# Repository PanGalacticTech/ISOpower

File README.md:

# ISOpowerProject
 Remote power control board for ISO experiment containers, used for remote labs projects

## Use

### Programming [See Issues]
 To Program AtMega328pb use the following settings:

### prog_power_select

- Jumper is used for power routing during programming
- Cut trace to main and solder USB to center to enable USB power during programming.
- Ensure to remove USB side and replace main for normal use

## Issues V1.0

1. Tx & Rx Pin swapped on CH340 - aTmeGA328P
 - To enable USB communication, reverse pins 2 & 3

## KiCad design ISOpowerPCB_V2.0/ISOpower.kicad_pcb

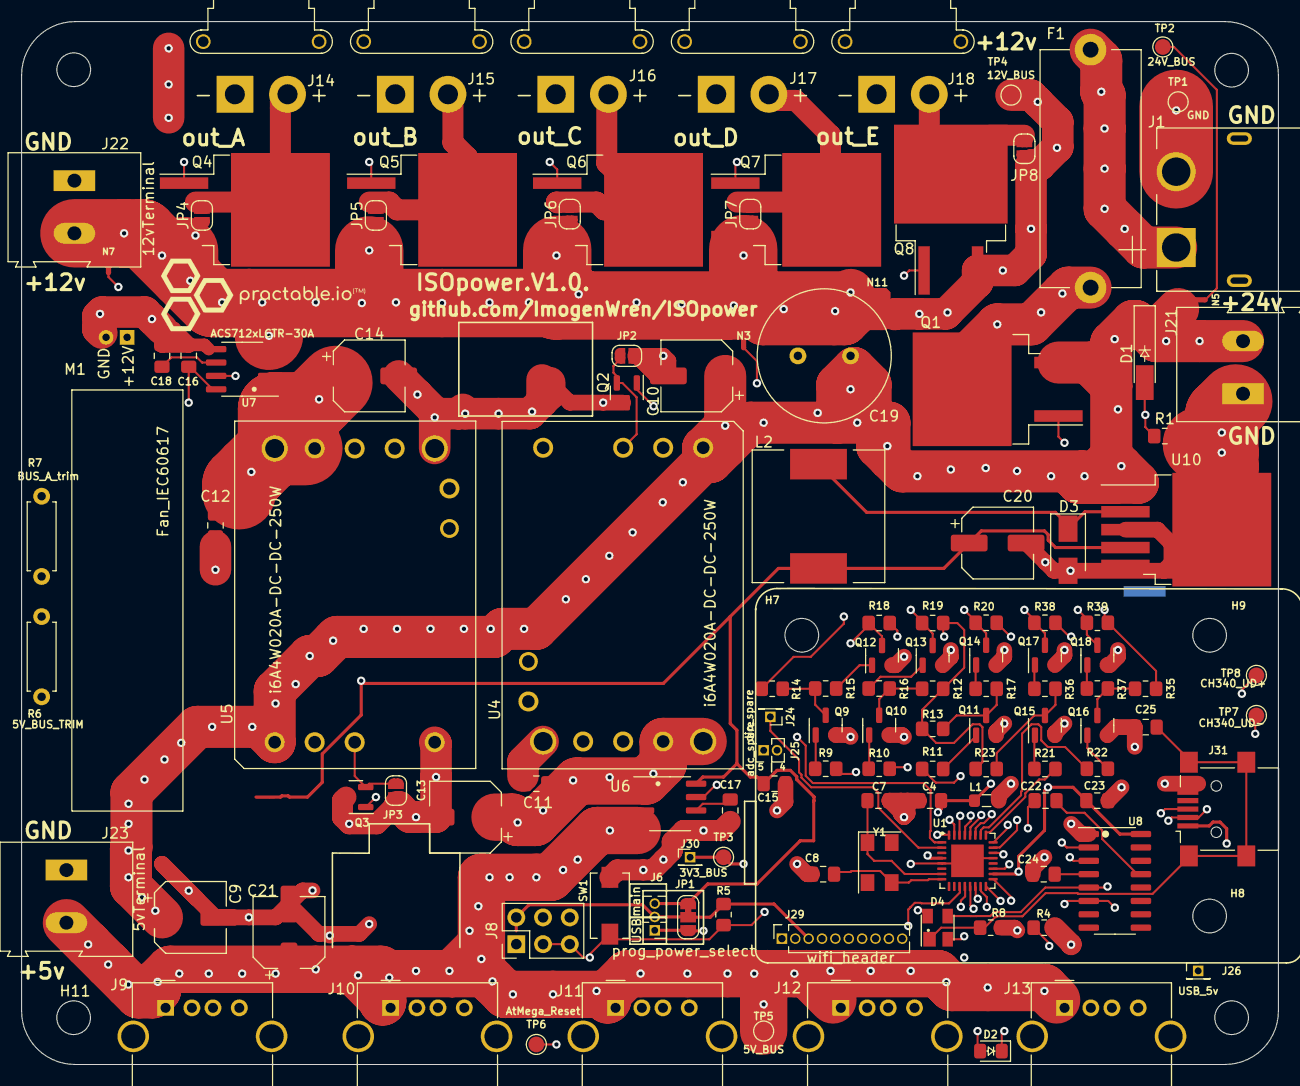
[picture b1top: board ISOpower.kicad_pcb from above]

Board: 4 copper layers, 119.4 x 99.1 mm, 128 parts (1 on the bottom side), 79 nets.

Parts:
C4, C11, C12, C15, C16, C22, C23, C24: 100n; C_0805_2012Metric_Pad1.18x1.45mm_HandSolder
C7, C8: 22p; C_0805_2012Metric_Pad1.18x1.45mm_HandSolder
C9, C10, C21: 100u; CP_Elec_6.3x7.7
C13, C14: 22u; CP_Elec_6.3x5.4
C17, C18: 1n; C_0805_2012Metric_Pad1.18x1.45mm_HandSolder
C19: 680u; C_Radial_D12.5mm_H20.0mm_P5.00mm
C20: 220u; CP_Elec_6.3x7.7
C25: 4n7; C_0805_2012Metric_Pad1.18x1.45mm_HandSolder
D1: BZV55B18; D_MiniMELF_Handsoldering
D2: Blue; LED_0805_2012Metric_Pad1.15x1.40mm_HandSolder
D3: 1N5821; D_SMA
D4: PRTR5V0U2X; SOT-143
F1: 20A; Fuseholder_Cylinder-5x20mm_Stelvio-Kontek_PTF78_Horizontal_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
H7, H8, H9: MountingHole; MountingHole_3.2mm_M3
H11: 2x2_ISOpower_mountingHoles; ISOpower_4xmounting_M3
J1: XT60_connector_DC_60A_male; AMASS_XT60PW-M
J6: prog_power_select; PinHeader_1x03_P1.27mm_Vertical
J8: AVR-ISP-6; AVR-ISP-header-02x03
J9, J10, J11, J12, J13: USB_CH_A; USB_A_Molex_67643_Horizontal
J14, J15, J16, J17, J18: XT30_connector_DC_30A_female; AMASS_XT30PW-F_1x02_P2.50mm_Horizontal
J21: 24vTerminal; TerminalBlock_Altech_AK300-2_P5.00mm
J22: 12vTerminal; TerminalBlock_Altech_AK300-2_P5.00mm
J23: 5vTerminal; TerminalBlock_Altech_AK300-2_P5.00mm
J24: dio_spare; PinHeader_1x01_P1.27mm_Vertical
J25: adc_spare; PinHeader_1x02_P1.27mm_Vertical
J26: USB_5v; PinHeader_1x01_P1.27mm_Vertical
J29: wifi_header; PinSocket_1x10_P1.27mm_Vertical
J30: 3V3_spare; PinHeader_1x01_P1.27mm_Vertical
J31: USB_B_Mini; USB_Mini-B_Lumberg_2486_01_Horizontal
JP1: prog_power_select; SolderJumper-3_P1.3mm_Bridged12_RoundedPad1.0x1.5mm_NumberL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
JP2: DSBL_BYPSS_B; SolderJumper-2_P1.3mm_Open_RoundedPad1.0x1.5mm
JP3: DSBL_BYPSS_A; SolderJumper-2_P1.3mm_Open_RoundedPad1.0x1.5mm
JP4: OP_0; SolderJumper-2_P1.3mm_Open_RoundedPad1.0x1.5mm
JP5: OP_1; SolderJumper-2_P1.3mm_Open_RoundedPad1.0x1.5mm
JP6: OP_2; SolderJumper-2_P1.3mm_Open_RoundedPad1.0x1.5mm
JP7: OP_3; SolderJumper-2_P1.3mm_Open_RoundedPad1.0x1.5mm
JP8: OP_4; SolderJumper-2_P1.3mm_Open_RoundedPad1.0x1.5mm
L1: 10uH; L_0805_2012Metric_Pad1.05x1.20mm_HandSolder
L2: 33uH; L_12x12mm_H8mm
M1: Fan_IEC60617; Fan12V_40by10.5mm
N3, N5, N7: Net_Tie; NetTie-2_SMD_Pad0.5mm
N6: Net_Tie; NetTie-8-15A_1oz_2oz
N11: pwr_tie; NetTie-8-15A_1oz_2oz_chamf
Q1, Q4, Q5, Q6, Q7, Q8: IRF5305_PBF; TO-263-2
Q2, Q3: Si2319CDS; SOT-23
Q9, Q10, Q11, Q12, Q13, Q14, Q15, Q16, Q17, Q18: BC817; SOT-23
R1, R4: 330r; R_0805_2012Metric_Pad1.20x1.40mm_HandSolder
R5, R9, R10, R11, R12, R13, R14, R15, R16, R17, R18, R19, R20, R21, R22, R23, R35, R36, R37, R38, R39: 10k; R_0805_2012Metric_Pad1.20x1.40mm_HandSolder
R6: 5V_BUS_TRIM; R_Axial_DIN0207_L6.3mm_D2.5mm_P7.62mm_Horizontal
R7: BUS_A_trim; R_Axial_DIN0207_L6.3mm_D2.5mm_P7.62mm_Horizontal
R8: 1M; R_0805_2012Metric_Pad1.20x1.40mm_HandSolder
SW1: SW_Push; SW_SPST_EVQPE1
TP1: GND; TestPoint_Pad_D1.5mm
TP2: 24V_BUS; TestPoint_Pad_D1.5mm
TP3: 3V3_BUS; TestPoint_Pad_D1.5mm
TP4: 12V_BUS; TestPoint_Pad_D1.5mm
TP5: 5V_BUS; TestPoint_Pad_D1.5mm
TP6: AtMega_Reset; TestPoint_Pad_D1.5mm
TP7: CH340_UD-; TestPoint_Pad_D1.5mm
TP8: CH340_UD+; TestPoint_Pad_D1.5mm
U1: ATmega3278PB-M; QFN-32-1EP_5x5mm_P0.5mm_EP3.1x3.1mm
U4, U5: i6A4W020A-DC-DC-250W; i6A4W-DIP
U6, U7: ACS712xLCTR-30A; SOIC-8_3.9x4.9mm_P1.27mm
U8: CH340C; SOIC-16_3.9x9.9mm_P1.27mm
U10: LM2596S-5; TO-263-5_TabPin3
Y1: 16MHz; Crystal_SMD_Abracon_ABM3C-4Pin_5.0x3.2mm

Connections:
5V_BUS: C21.1, J9.1 (VBUS), J10.1 (VBUS), J11.1 (VBUS), J12.1 (VBUS), J13.1 (VBUS), J23.2, TP5.1, U6.3 (IP-), U6.4 (IP-)
12V_BUS: J22.2, JP4.1 (A), JP5.1 (A), JP6.1 (A), JP7.1 (A), N3.2 (C), N7.2 (C), N11.1 (A), Q4.3 (S), Q5.3 (S), Q6.3 (S), Q7.3 (S), U7.3 (IP-), U7.4 (IP-)
24V_BUS: C9.1, C10.1, C19.1, D1.1 (K), J21.2, N5.2 (C), Q1.3 (S), U4.1 (Vin(+)), U5.1 (Vin(+)), U10.1 (VIN)
/3V3_BUS: J29.2, J30.1, TP3.1
/24V_0: F1.1, J1.2 (V+)
/24V_1: F1.2, Q1.2 (D)
/AtMega328p/ADC4: J25.2, U1.27 (PC4)
/AtMega328p/ADC5: J25.1, U1.28 (PC5)
/AtMega328p/CH_C: J24.1, U1.2 (PD4)
/AtMega328p/CH_F: R9.1, U1.14 (PB2)
/AtMega328p/CH_G: R10.1, U1.23 (PC0)
/AtMega328p/CH_H: R11.1, U1.24 (PC1)
/AtMega328p/CH_I: R21.1, U1.25 (PC2)
/AtMega328p/CH_J: R22.1, U1.26 (PC3)
/AtMega328p/MCU_5V_BUS: C4.1, C23.1, D4.4 (VCC), J6.2, J8.2 (VCC), J29.3, JP1.2 (C), L1.1, R5.1, U1.4 (VCC), U1.18 (AVCC), U8.16 (VCC)
/AtMega328p/SSERIAL_RX: J29.10, U1.13 (PB1)
/AtMega328p/SSERIAL_TX: J29.9, U1.12 (PB0)
/AtMega328p/USB MCU CH340 Interface A/DTR_A: C22.1, J8.5 (~RST), R5.2, SW1.1, TP6.1, U1.29 (~RESET/PC6)
/AtMega328p/USB MCU CH340 Interface A/RxD_A: U1.31 (PD1/TX), U8.3 (RXD)
/AtMega328p/USB MCU CH340 Interface A/TxD_A: U1.30 (PD0/RX), U8.2 (TXD)
/BUS_A_DISABLE: Q3.1 (G), U1.32 (PD2)
/BUS_B_DISABLE: Q2.1 (G), U1.1 (PD3)
/BUS_I_SENSE_A: U1.22 (PE3), U7.7 (VIOUT)
/BUS_I_SENSE_B: U1.19 (PE2), U6.7 (VIOUT)
/MCU_5V: C15.1, C16.1, C20.1, J6.3, JP1.1 (A), L2.2, U6.8 (VCC), U7.8 (VCC), U10.4 (FB)
/Power Distribution/5V_I_SENSE_IP: C11.1, C13.1, U4.7 (Sense(+)), U4.8 (Vout(+)), U6.1 (IP+), U6.2 (IP+)
/Power Distribution/12V_I_SENSE_IP: C12.1, C14.1, U5.7 (Sense(+)), U5.8 (Vout(+)), U7.1 (IP+), U7.2 (IP+)
/Power Outputs/5v to 12v logic conversion_v2/0_OUT: Q4.1 (G), Q12.3 (C), R18.1
/Power Outputs/5v to 12v logic conversion_v2/1_OUT: Q5.1 (G), Q13.3 (C), R19.1
/Power Outputs/5v to 12v logic conversion_v2/2_OUT: Q6.1 (G), Q14.3 (C), R20.1
/Power Outputs/5v to 12v logic conversion_v2/3_OUT: Q7.1 (G), Q17.3 (C), R38.1
/Power Outputs/5v to 12v logic conversion_v2/4_OUT: Q8.1 (G), Q18.3 (C), R39.1
/Power Outputs/12V_OP_0: J14.2 (V+), JP4.2 (B), Q4.2 (D)
/Power Outputs/12V_OP_1: J15.2 (V+), JP5.2 (B), Q5.2 (D)
/Power Outputs/12V_OP_2: J16.2 (V+), JP6.2 (B), Q6.2 (D)
/Power Outputs/12V_OP_3: J17.2 (V+), JP7.2 (B), Q7.2 (D)
/Power Outputs/12V_OP_4: J18.2 (V+), JP8.2 (B), Q8.2 (D)
/Power Outputs/MID_PWR: JP8.1 (A), N11.2 (C), Q8.3 (S), TP4.1
/USB_PBUS: J6.1, J26.1, J29.4, J31.1 (VBUS), JP1.3 (B)
GND: C4.2, C7.2, C8.2, C15.2, C23.2, C24.2, C25.1, J29.1, J31.5 (GND), L1.2, N6.2 (C), Q9.2 (E), Q10.2 (E), Q11.2 (E), Q12.2 (E), Q13.2 (E), Q14.2 (E), Q15.2 (E), Q16.2 (E), Q17.2 (E), Q18.2 (E), R4.2, R8.2, U1.5 (GND), U1.21 (GND), U1.33 (GND), U8.1 (GND)
GNDPWR: C9.2, C10.2, C11.2, C12.2, C13.2, C14.2, C16.2, C17.2, C18.2, C19.2, C20.2, C21.2, D3.2 (A), J1.1 (V-), J8.6 (GND), J9.4 (GND), J9.5 (Shield), J10.4 (GND), J10.5 (Shield), J11.4 (GND), J11.5 (Shield), J12.4 (GND), J12.5 (Shield), J13.4 (GND), J13.5 (Shield), J14.1 (V-), J15.1 (V-), J16.1 (V-), J17.1 (V-), J18.1 (V-), J21.1, J22.1, J23.1, JP2.1 (A), JP3.1 (A), M1.2 (-), N6.1 (A), Q2.3 (D), Q3.3 (D), R1.2, R6.2, R7.2, SW1.2, TP1.1, U4.3 (Vin(-)), U4.4 (Vout(-)), U5.3 (Vin(-)), U5.4 (Vout(-)), U6.5 (GND), U7.5 (GND), U10.3 (GND), U10.5 (~ON/OFF)
HV: N3.1 (A), R12.2, R13.2, R14.2, R18.2, R19.2, R20.2, R23.2, R35.2, R38.2, R39.2
unnamed: C7.1, U1.7 (XTAL1/PB6), Y1.1
unnamed: C8.1, U1.8 (XTAL2/PB7), Y1.3
unnamed: C17.1, U6.6 (FILTER)
unnamed: C18.1, U7.6 (FILTER)
unnamed: C22.2, U8.13 (~DTR)
unnamed: C24.1, U8.4 (V3)
unnamed: C25.2, D4.1 (GND), J31.6 (Shield), R8.1
unnamed: D1.2 (A), Q1.1 (G), R1.1
unnamed: D2.1 (K), R4.1
unnamed: D2.2 (A), U1.11 (PD7)
unnamed: D3.1 (K), L2.1, U10.2 (OUT)
unnamed: D4.2 (I/O1), J31.2 (D-), TP7.1, U8.6 (UD-)
unnamed: D4.3 (I/O2), J31.3 (D+), TP8.1, U8.5 (UD+)
unnamed: J8.1 (MISO), U1.16 (PB4)
unnamed: J8.3 (SCK), U1.17 (PB5)
unnamed: J8.4 (MOSI), U1.15 (PB3)
unnamed: JP2.2 (B), Q2.2 (S), U4.2 (On/Off)
unnamed: JP3.2 (B), Q3.2 (S), U5.2 (On/Off)
unnamed: M1.1 (+), N7.1 (A)
unnamed: N5.1 (A), TP2.1
unnamed: Q9.1 (B), R9.2
unnamed: Q9.3 (C), R14.1, R15.1
unnamed: Q10.1 (B), R10.2
unnamed: Q10.3 (C), R12.1, R16.1
unnamed: Q11.1 (B), R11.2
unnamed: Q11.3 (C), R13.1, R17.1
unnamed: Q12.1 (B), R15.2
unnamed: Q13.1 (B), R16.2
unnamed: Q14.1 (B), R17.2
unnamed: Q15.1 (B), R21.2
unnamed: Q15.3 (C), R23.1, R36.1
unnamed: Q16.1 (B), R22.2
unnamed: Q16.3 (C), R35.1, R37.1
unnamed: Q17.1 (B), R36.2
unnamed: Q18.1 (B), R37.2
unnamed: R6.1, U4.6 (Trim)
unnamed: R7.1, U5.6 (Trim)

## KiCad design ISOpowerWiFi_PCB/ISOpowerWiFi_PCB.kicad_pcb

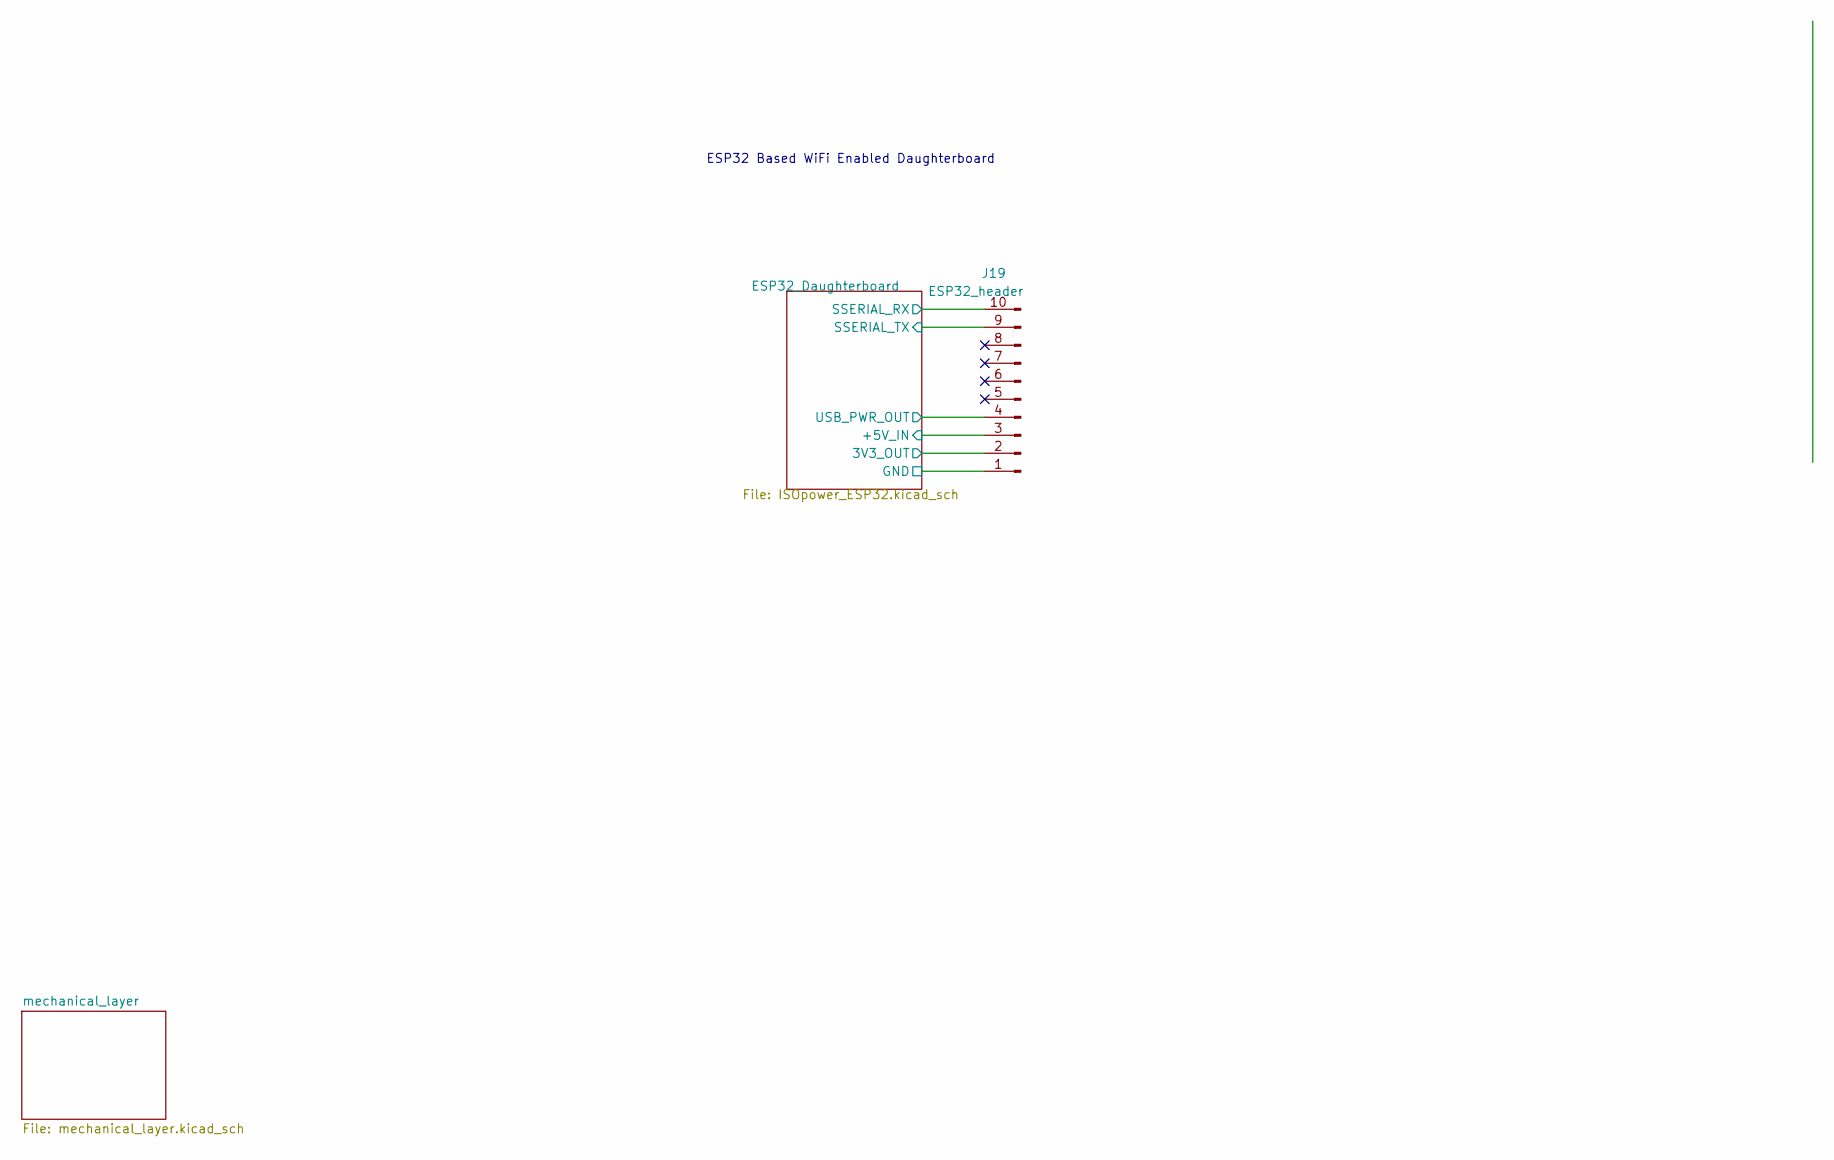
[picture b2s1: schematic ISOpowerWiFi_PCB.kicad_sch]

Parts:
J19: ESP32_header; PinHeader_1x10_P1.27mm_Vertical

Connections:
/ESP32_Daughterboard/3V3_BUS: J19.2; also elsewhere on the board
/ESP32_Daughterboard/GND: J19.1; also elsewhere on the board
/ESP32_Daughterboard/MCU_5V_BUS: J19.3; also elsewhere on the board
/ESP32_Daughterboard/SSERIAL_RX: J19.10; also elsewhere on the board
/ESP32_Daughterboard/SSERIAL_TX: J19.9; also elsewhere on the board
/ESP32_Daughterboard/USB_PBUS: J19.4; also elsewhere on the board

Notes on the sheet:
ESP32 Based WiFi Enabled Daughterboard

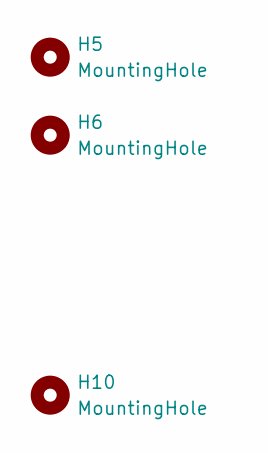
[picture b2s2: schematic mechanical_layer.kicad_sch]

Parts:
H5, H6, H10: MountingHole; MountingHole_3.2mm_M3

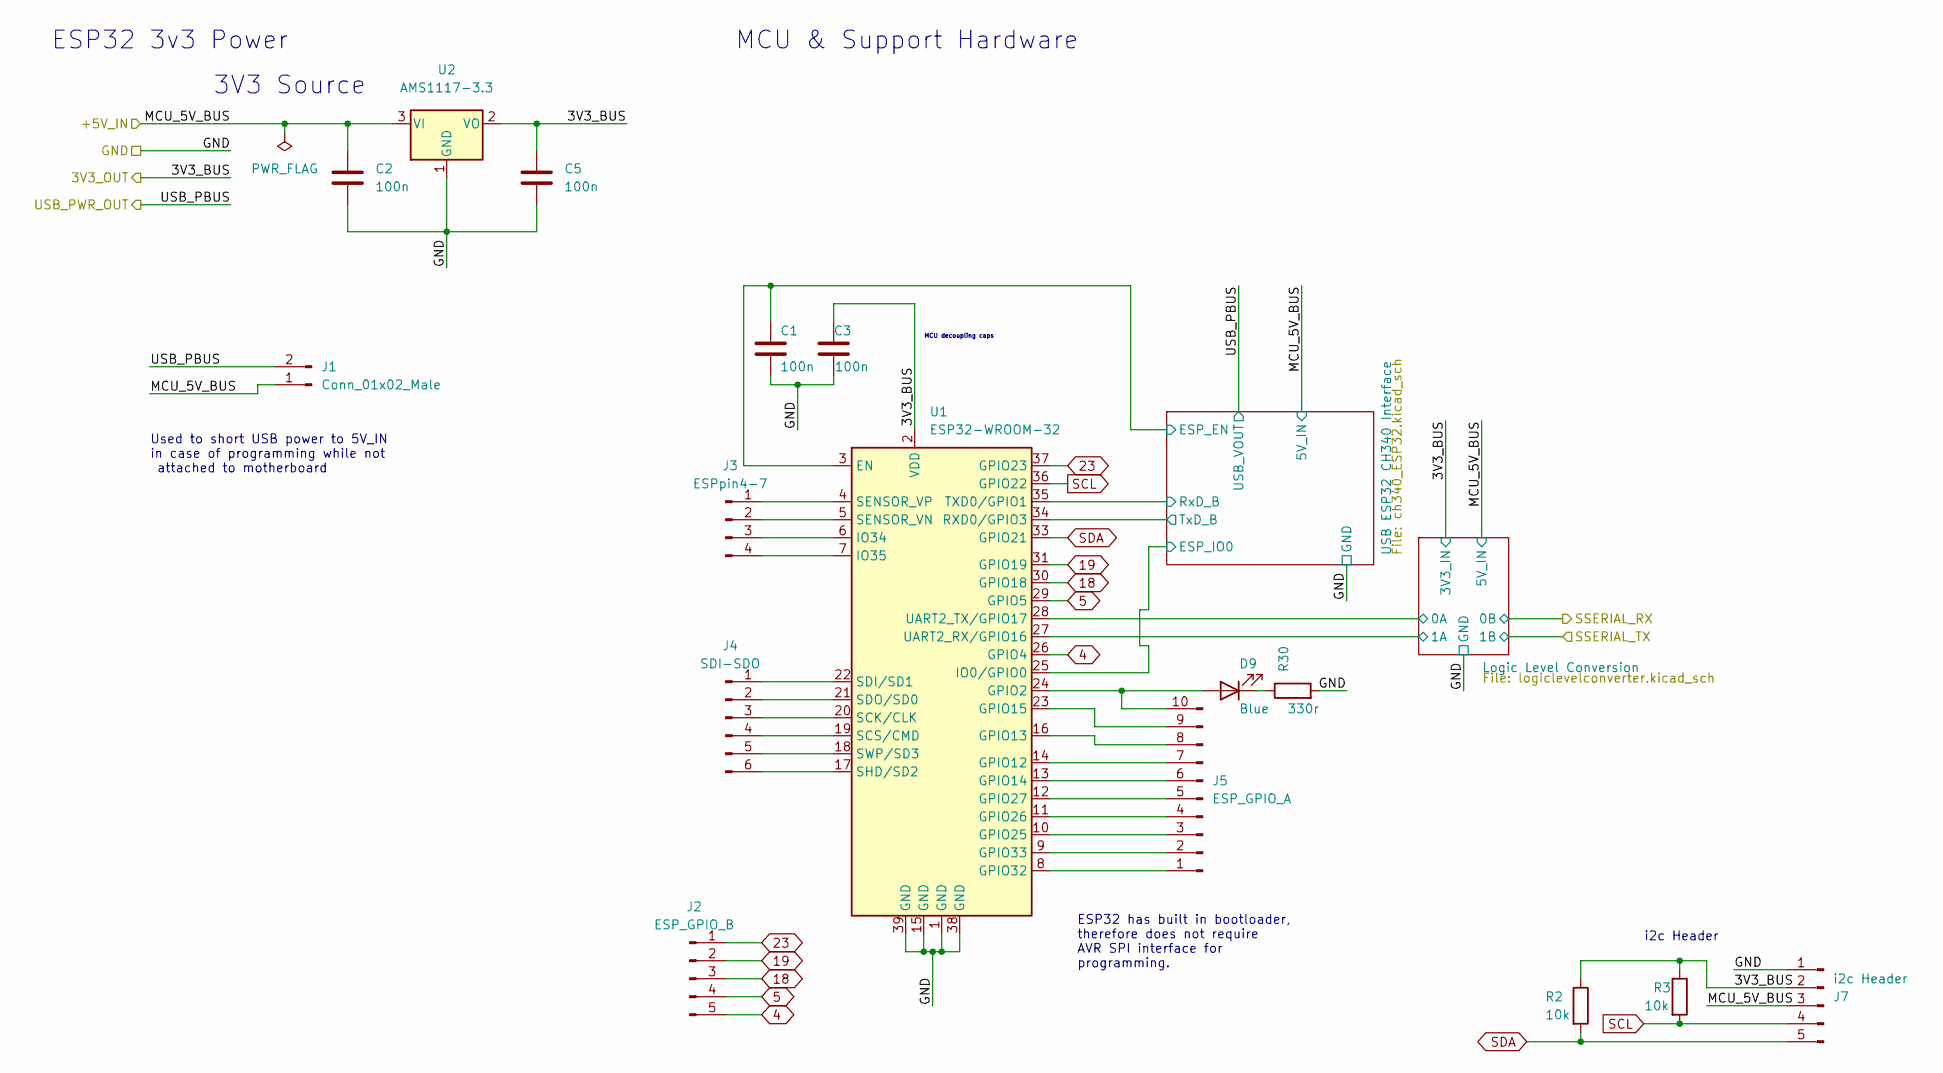
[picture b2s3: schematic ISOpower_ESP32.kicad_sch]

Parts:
C1, C2, C3, C5: 100n; C_0805_2012Metric_Pad1.18x1.45mm_HandSolder
D9: Blue; LED_0805_2012Metric_Pad1.15x1.40mm_HandSolder
J1: Conn_01x02_Male; PinHeader_1x02_P1.27mm_Vertical
J2: ESP_GPIO_B; PinHeader_1x05_P1.27mm_Vertical
J3: ESPpin4-7; PinHeader_1x04_P1.27mm_Vertical
J4: SDI-SDO; PinHeader_1x06_P1.27mm_Vertical
J5: ESP_GPIO_A; PinHeader_1x10_P1.27mm_Vertical
J7: i2c Header; PinHeader_1x05_P1.27mm_Vertical
R2, R3: 10k; R_0805_2012Metric_Pad1.20x1.40mm_HandSolder
R30: 330r; R_0805_2012Metric_Pad1.20x1.40mm_HandSolder
U1: ESP32-WROOM-32
U2: AMS1117-3.3; SOT-223-3_TabPin2

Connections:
4: J2.5, U1.26 (GPIO4)
5: J2.4, U1.29 (GPIO5)
18: J2.3, U1.30 (GPIO18)
19: J2.2, U1.31 (GPIO19)
23: J2.1, U1.37 (GPIO23)
/ESP32_Daughterboard/3V3_BUS: C3.1, C5.1, J7.2, R2.1, R3.1, U1.2 (VDD), U2.2 (VO); also elsewhere on the board
/ESP32_Daughterboard/GND: C1.2, C2.2, C3.2, C5.2, J7.1, R30.2, U1.1 (GND), U1.15 (GND), U1.38 (GND), U1.39 (GND), U2.1 (GND); also elsewhere on the board
/ESP32_Daughterboard/Logic Level Conversion/0A: U1.28 (UART2_TX/GPIO17); also elsewhere on the board
/ESP32_Daughterboard/Logic Level Conversion/1A: U1.27 (UART2_RX/GPIO16); also elsewhere on the board
/ESP32_Daughterboard/MCU_5V_BUS: C2.1, J1.1, J7.3, U2.3 (VI); also elsewhere on the board
/ESP32_Daughterboard/USB ESP32 CH340 Interface /ESP_EN: C1.1, U1.3 (EN); also elsewhere on the board
/ESP32_Daughterboard/USB ESP32 CH340 Interface /ESP_IO0: U1.25 (IO0/GPIO0); also elsewhere on the board
/ESP32_Daughterboard/USB ESP32 CH340 Interface /RxD_B: U1.35 (TXD0/GPIO1); also elsewhere on the board
/ESP32_Daughterboard/USB ESP32 CH340 Interface /TxD_B: U1.34 (RXD0/GPIO3); also elsewhere on the board
/ESP32_Daughterboard/USB_PBUS: J1.2; also elsewhere on the board
unnamed: D9.1 (K), R30.1
unnamed: D9.2 (A), J5.10, U1.24 (GPIO2)
unnamed: J3.1, U1.4 (SENSOR_VP)
unnamed: J3.2, U1.5 (SENSOR_VN)
unnamed: J3.3, U1.6 (IO34)
unnamed: J3.4, U1.7 (IO35)
unnamed: J4.1, U1.22 (SDI/SD1)
unnamed: J4.2, U1.21 (SDO/SD0)
unnamed: J4.3, U1.20 (SCK/CLK)
unnamed: J4.4, U1.19 (SCS/CMD)
unnamed: J4.5, U1.18 (SWP/SD3)
unnamed: J4.6, U1.17 (SHD/SD2)
unnamed: J5.1, U1.8 (GPIO32)
unnamed: J5.2, U1.9 (GPIO33)
unnamed: J5.3, U1.10 (GPIO25)
unnamed: J5.4, U1.11 (GPIO26)
unnamed: J5.5, U1.12 (GPIO27)
unnamed: J5.6, U1.13 (GPIO14)
unnamed: J5.7, U1.14 (GPIO12)
unnamed: J5.8, U1.16 (GPIO13)
unnamed: J5.9, U1.23 (GPIO15)
SCL: J7.4, R3.2, U1.36 (GPIO22)
SDA: J7.5, R2.2, U1.33 (GPIO21)

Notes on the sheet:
MCU & Support Hardware
MCU decoupling caps
ESP32 3v3 Power
ESP32 has built in bootloader, therefore does not require AVR SPI interface for programming.
3V3 Source
Used to short USB power to 5V_IN in case of programming while not attached to motherboard
i2c Header

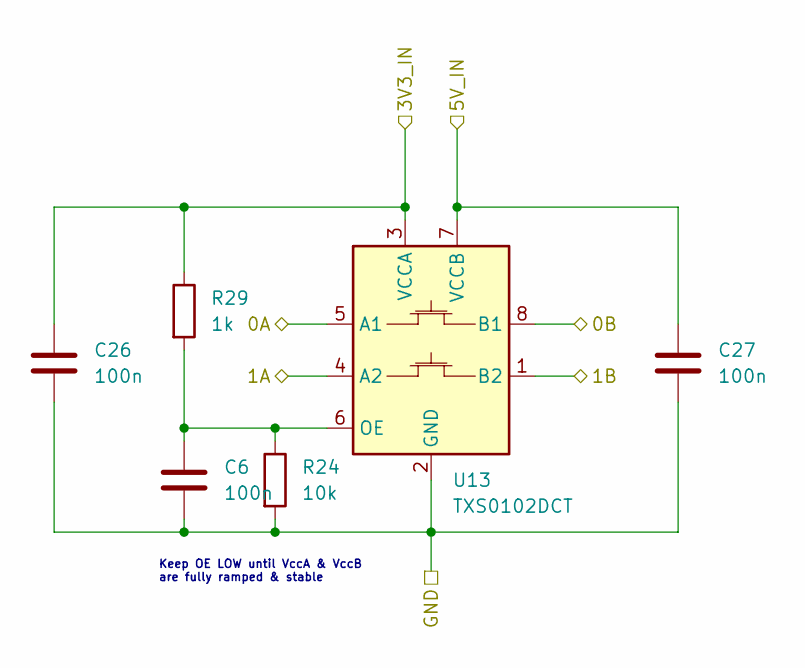
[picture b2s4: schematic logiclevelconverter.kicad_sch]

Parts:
C6, C26, C27: 100n; C_0805_2012Metric_Pad1.18x1.45mm_HandSolder
R24: 10k; R_0805_2012Metric_Pad1.20x1.40mm_HandSolder
R29: 1k; R_0805_2012Metric_Pad1.20x1.40mm_HandSolder
U13: TXS0102DCT; SSOP-8_2.95x2.8mm_P0.65mm

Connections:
/ESP32_Daughterboard/3V3_BUS: C26.1, R29.1, U13.3 (VCCA); also elsewhere on the board
/ESP32_Daughterboard/GND: C6.2, C26.2, C27.2, R24.2, U13.2 (GND); also elsewhere on the board
/ESP32_Daughterboard/Logic Level Conversion/0A: U13.5 (A1); also elsewhere on the board
/ESP32_Daughterboard/Logic Level Conversion/1A: U13.4 (A2); also elsewhere on the board
/ESP32_Daughterboard/MCU_5V_BUS: C27.1, U13.7 (VCCB); also elsewhere on the board
/ESP32_Daughterboard/SSERIAL_RX: U13.8 (B1); also elsewhere on the board
/ESP32_Daughterboard/SSERIAL_TX: U13.1 (B2); also elsewhere on the board
unnamed: C6.1, R24.1, R29.2, U13.6 (OE)

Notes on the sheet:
Keep OE LOW until VccA & VccB are fully ramped & stable

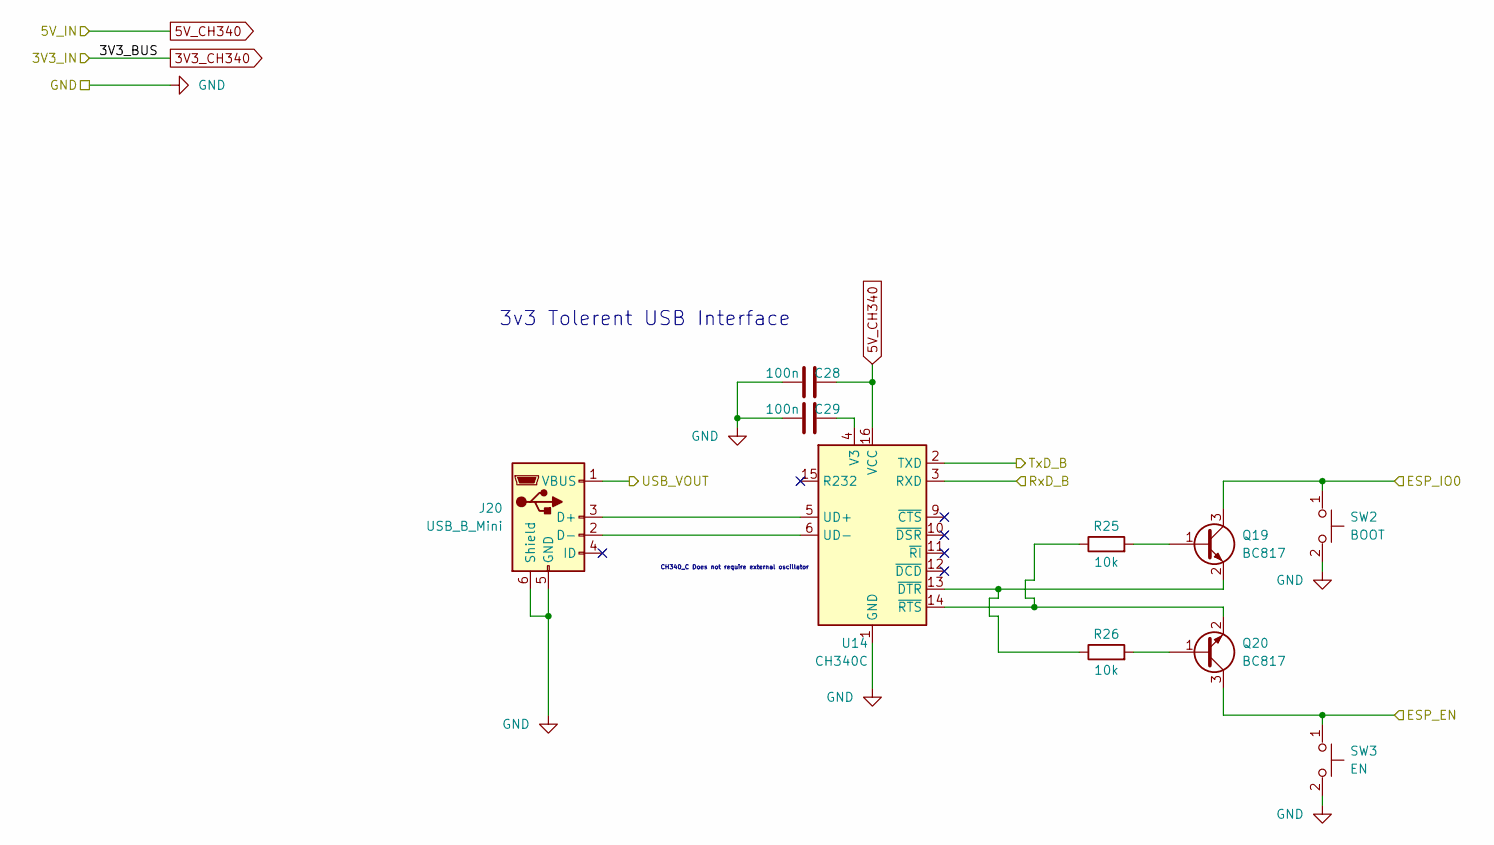
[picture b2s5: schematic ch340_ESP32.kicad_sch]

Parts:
C28, C29: 100n; C_0805_2012Metric_Pad1.18x1.45mm_HandSolder
J20: USB_B_Mini; USB_Mini-B_Lumberg_2486_01_Horizontal
Q19, Q20: BC817; SOT-23
R25, R26: 10k; R_0805_2012Metric_Pad1.20x1.40mm_HandSolder
SW2: BOOT; SW_SPST_EVQPE1
SW3: EN; SW_SPST_EVQPE1
U14: CH340C; SOIC-16_3.9x9.9mm_P1.27mm

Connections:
/ESP32_Daughterboard/GND: C28.2, C29.2, J20.5 (GND), J20.6 (Shield), SW2.2, SW3.2, U14.1 (GND); also elsewhere on the board
/ESP32_Daughterboard/MCU_5V_BUS: C28.1, U14.16 (VCC); also elsewhere on the board
/ESP32_Daughterboard/USB ESP32 CH340 Interface /ESP_EN: Q20.3 (C), SW3.1; also elsewhere on the board
/ESP32_Daughterboard/USB ESP32 CH340 Interface /ESP_IO0: Q19.3 (C), SW2.1; also elsewhere on the board
/ESP32_Daughterboard/USB ESP32 CH340 Interface /RxD_B: U14.3 (RXD); also elsewhere on the board
/ESP32_Daughterboard/USB ESP32 CH340 Interface /TxD_B: U14.2 (TXD); also elsewhere on the board
/ESP32_Daughterboard/USB_PBUS: J20.1 (VBUS); also elsewhere on the board
unnamed: C29.1, U14.4 (V3)
unnamed: J20.2 (D-), U14.6 (UD-)
unnamed: J20.3 (D+), U14.5 (UD+)
unnamed: Q19.1 (B), R25.2
unnamed: Q19.2 (E), R26.1, U14.13 (~DTR)
unnamed: Q20.1 (B), R26.2
unnamed: Q20.2 (E), R25.1, U14.14 (~RTS)

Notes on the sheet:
3v3 Tolerent USB Interface
CH340_C Does not require external oscillator

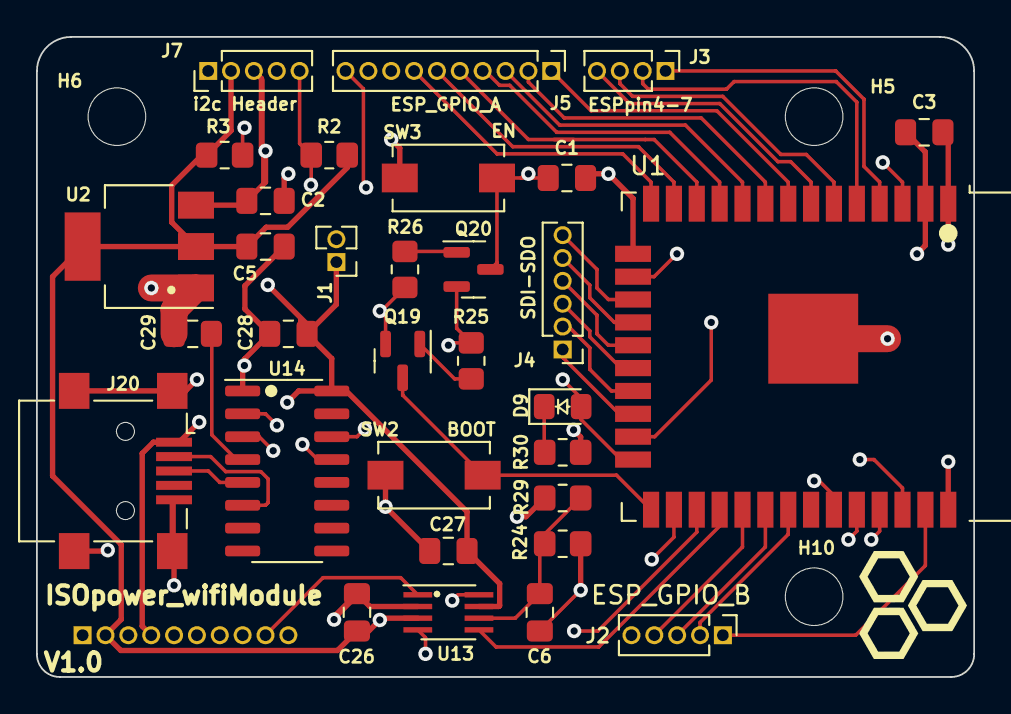
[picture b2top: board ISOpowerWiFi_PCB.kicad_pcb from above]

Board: 4 copper layers, 52.1 x 35.6 mm, 36 parts (1 on the bottom side), 48 nets.

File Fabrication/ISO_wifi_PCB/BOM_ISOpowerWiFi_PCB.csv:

Ref,Qnty,Value,Cmp name,Footprint,JLCPCB Part #,Description
,,,,,,
"C1, C2, C3, C5, C6, C26, C27, C28, C29, ",9,100n,cap_film_0805,Capacitor_SMD:C_0805_2012Metric_Pad1.18x1.45mm_HandSolder,C49678,
,,,,,,
"D9, ",1,Blue,LED_0805_smd,LED_SMD:LED_0805_2012Metric_Pad1.15x1.40mm_HandSolder,C138557,Light emitting diode
,,,,,,
"J20, ",1,USB_B_Mini,USB_B_Mini,Connector_USB:USB_Mini-B_Lumberg_2486_01_Horizontal,C2681563,USB Mini Type B connector
,,,,,,
"Q19, Q20, ",2,BC817,BC817,Package_TO_SOT_SMD:SOT-23,C181151,"0.8A Ic, 45V Vce, NPN Transistor, SOT-23"
,,,,,,
"R2, R3, R24, R25, R26, ",5,10k,Resistor_0805,Resistor_SMD:R_0805_2012Metric_Pad1.20x1.40mm_HandSolder,C17414,
,,,,,,
"R29, ",1,1k,Resistor_0805,Resistor_SMD:R_0805_2012Metric_Pad1.20x1.40mm_HandSolder,C17513,Resistor
,,,,,,
"R30, ",1,330r,Resistor_0805,Resistor_SMD:R_0805_2012Metric_Pad1.20x1.40mm_HandSolder,C17630,Resistor
,,,,,,
"SW2, ",1,BOOT,pushbutton_tactile_2pin_SMD,Button_Switch_SMD:SW_SPST_EVQPE1,C455280,MEC 5E single pole normally-open tactile switch
,,,,,,
"SW3, ",1,EN,pushbutton_tactile_2pin_SMD,Button_Switch_SMD:SW_SPST_EVQPE1,C455280,MEC 5E single pole normally-open tactile switch
,,,,,,
"U1, ",1,ESP32-WROOM-32,ESP32-WROOM-32,RF_Module:ESP32-WROOM-32,C328062,"RF Module, ESP32-D0WDQ6 SoC, Wi-Fi 802.11b/g/n, Bluetooth, BLE, 32-bit, 2.7-3.6V, onboard antenna, SMD"
,,,,,,
"U2, ",1,AMS1117-3.3,AMS1117-3.3,Package_TO_SOT_SMD:SOT-223-3_TabPin2,C6186,"1A Low Dropout regulator, positive, 3.3V fixed output, SOT-223"
,,,,,,
"U13, ",1,TXS0102DCT,TXS0102DCT,Package_SO:SSOP-8_2.95x2.8mm_P0.65mm,C324082,"2-Bit Bidirectional Voltage-Level Shifter for Open-Drain and Push-Pull Application, SSOP-8"
,,,,,,
"U14, ",1,CH340C,CH340C,Package_SO:SOIC-16_3.9x9.9mm_P1.27mm,C84681,"USB serial converter, UART, SOIC-16"

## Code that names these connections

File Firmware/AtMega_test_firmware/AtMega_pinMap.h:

/*  AtMega_pinMap.h

     Translates schematic pin numbers into Arduino digital pin numbers
     and register numbers for pins not available on arduino nano board




*/

#ifndef AtMega_pinMap_h
#define AtMega_pinMap_h



  
#define BUS_12V_DISABLE        2       // HIGH to Disable - I Think
#define BUS_5V_DISABLE         3       // HIGH to Disable
#define CH_C                   4

#define BUS_5V_MONITOR         5       //BUS_5V_MONITOR
#define BUS_12V_MONITOR        6       // BUS_12V_MONITOR

#define LED_PIN               7  


 //Depreciated but not harming anybody
#define CH_A                  2        //BUS_12V_DISABLE              // HIGH to Disable
#define CH_B                  3        //BUS_5V_DISABLE               // HIGH to Disable
#define CH_C                  4

#define IN_D                  5        //BUS_5V_MONITOR
#define IN_E                  6        //BUS_12V_MONITOR

        

// Experiment Output Channels         // HIGH to Disable- (I Think)
#define CH_F                  10
#define CH_G                  A0
#define CH_H                  A1
#define CH_I                  A2
#define CH_J                  A3

int outputChannels[5] = {CH_F, CH_G, CH_H, CH_I, CH_J} ;

#define ADC4                  A4             //Spare
#define ADC5                  A5             //Spare

#define CURRENT_SENSE_12V     A6
#define CURRENT_SENSE_5V      A7






#endif

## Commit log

2022-01-24 Reoganised files
2022-01-25 deleted old backups & added documentation
2022-01-25 added updated docs
2022-01-25 modified pcb files
2022-01-26 Finished initial circuit design
2022-01-26 PCB Notes added
2022-01-28 Last commit before major changes
2022-01-28 Copied old version into version_0.1 folder
2022-01-28 Major schematic revisions
2022-01-31 significant changes
2022-02-04 Updated as per discussions 26/01/22
    # Change Notes
    04/02/2022
    As per discussion 26/01/22
    1. Changed per channel 5v MOSFET switches to MOSFET control of DC/DC module on/off pin - due to failure of MOSFET switching during testing.
    2. Added 5v buck converter for independent MCU_5V power bus.
    - Ensured all 5v MCU hardware is powered from common MCU_5V bus.
2022-02-14 Something
2022-02-14 messing around with libraries
2022-02-14 added local libraries
2022-02-14 adding logic for fault indication
2022-02-15 added how to diagram with mermaid example
2022-02-15 uurgh libraries
2022-02-15 temp files changes
2022-02-15 fixed most electrical rules check violations
2022-02-16 Footprint Associations 50% complete
2022-02-18 added documentation for component selection
    Completed footprint association & added documentation re Netclasses. Need to update netclasses in schematic settings before moving to PCB layout.
2022-02-21 Removed Optical Engine
    Folder inadvertently placed incorrectly
2022-02-21 added netclasses
2022-02-21 sdfsd
2022-02-21 Started PCB Layout
2022-02-22 Updated Changelog
2022-02-22 PCB Layouts
2022-02-23 Components placed V1.0
2022-02-24 Started Routing V1
2022-02-25 PCB layout completed.
    Screenshots added to media folder
2022-02-25 added media
2022-02-28 finished PCB design. Started design review docs
2022-03-01 Replacing power bus RE current draw issue
2022-03-02 almost finished needs to pass DRC check and fix aesthetics
2022-03-02 sdfs
2022-03-03 Finished Silkscreen edits
2022-03-03 Passed DRC - Board separation into 2 folders next
2022-03-03 Producing files for fabrication
2022-03-04 colating fabrication documents.
2022-03-04 hbvgkj
2022-03-07 Adding fabrication files
2022-03-16 added fabrication files
2022-03-25 updated BOM due to semiconductor shortages
2022-05-13 added first production photos
2022-05-24 added fabrication photos
2022-06-08 added firmware folder
2022-06-08 changes to ACS712 Current sense
2022-06-09 firmware for testing basic IO added
2022-06-16 Just some typos corrected
2022-06-16 blegh
2022-06-16 UPDATEZ
2022-06-17 Update Wifi_Test.ino
    changed some basic issues with the code
2022-06-20 UART Test
2022-06-21 sdcf
2022-07-08 ew534
2022-09-26 Started work on V2.0
2023-02-17 lots of stuffwork
2023-04-26 Maybe changed some references while copying footprints for updated version
2025-01-22 updating-update-repo
